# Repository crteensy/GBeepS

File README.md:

# GBeepS
GPS / Buzzer combo with backup supply

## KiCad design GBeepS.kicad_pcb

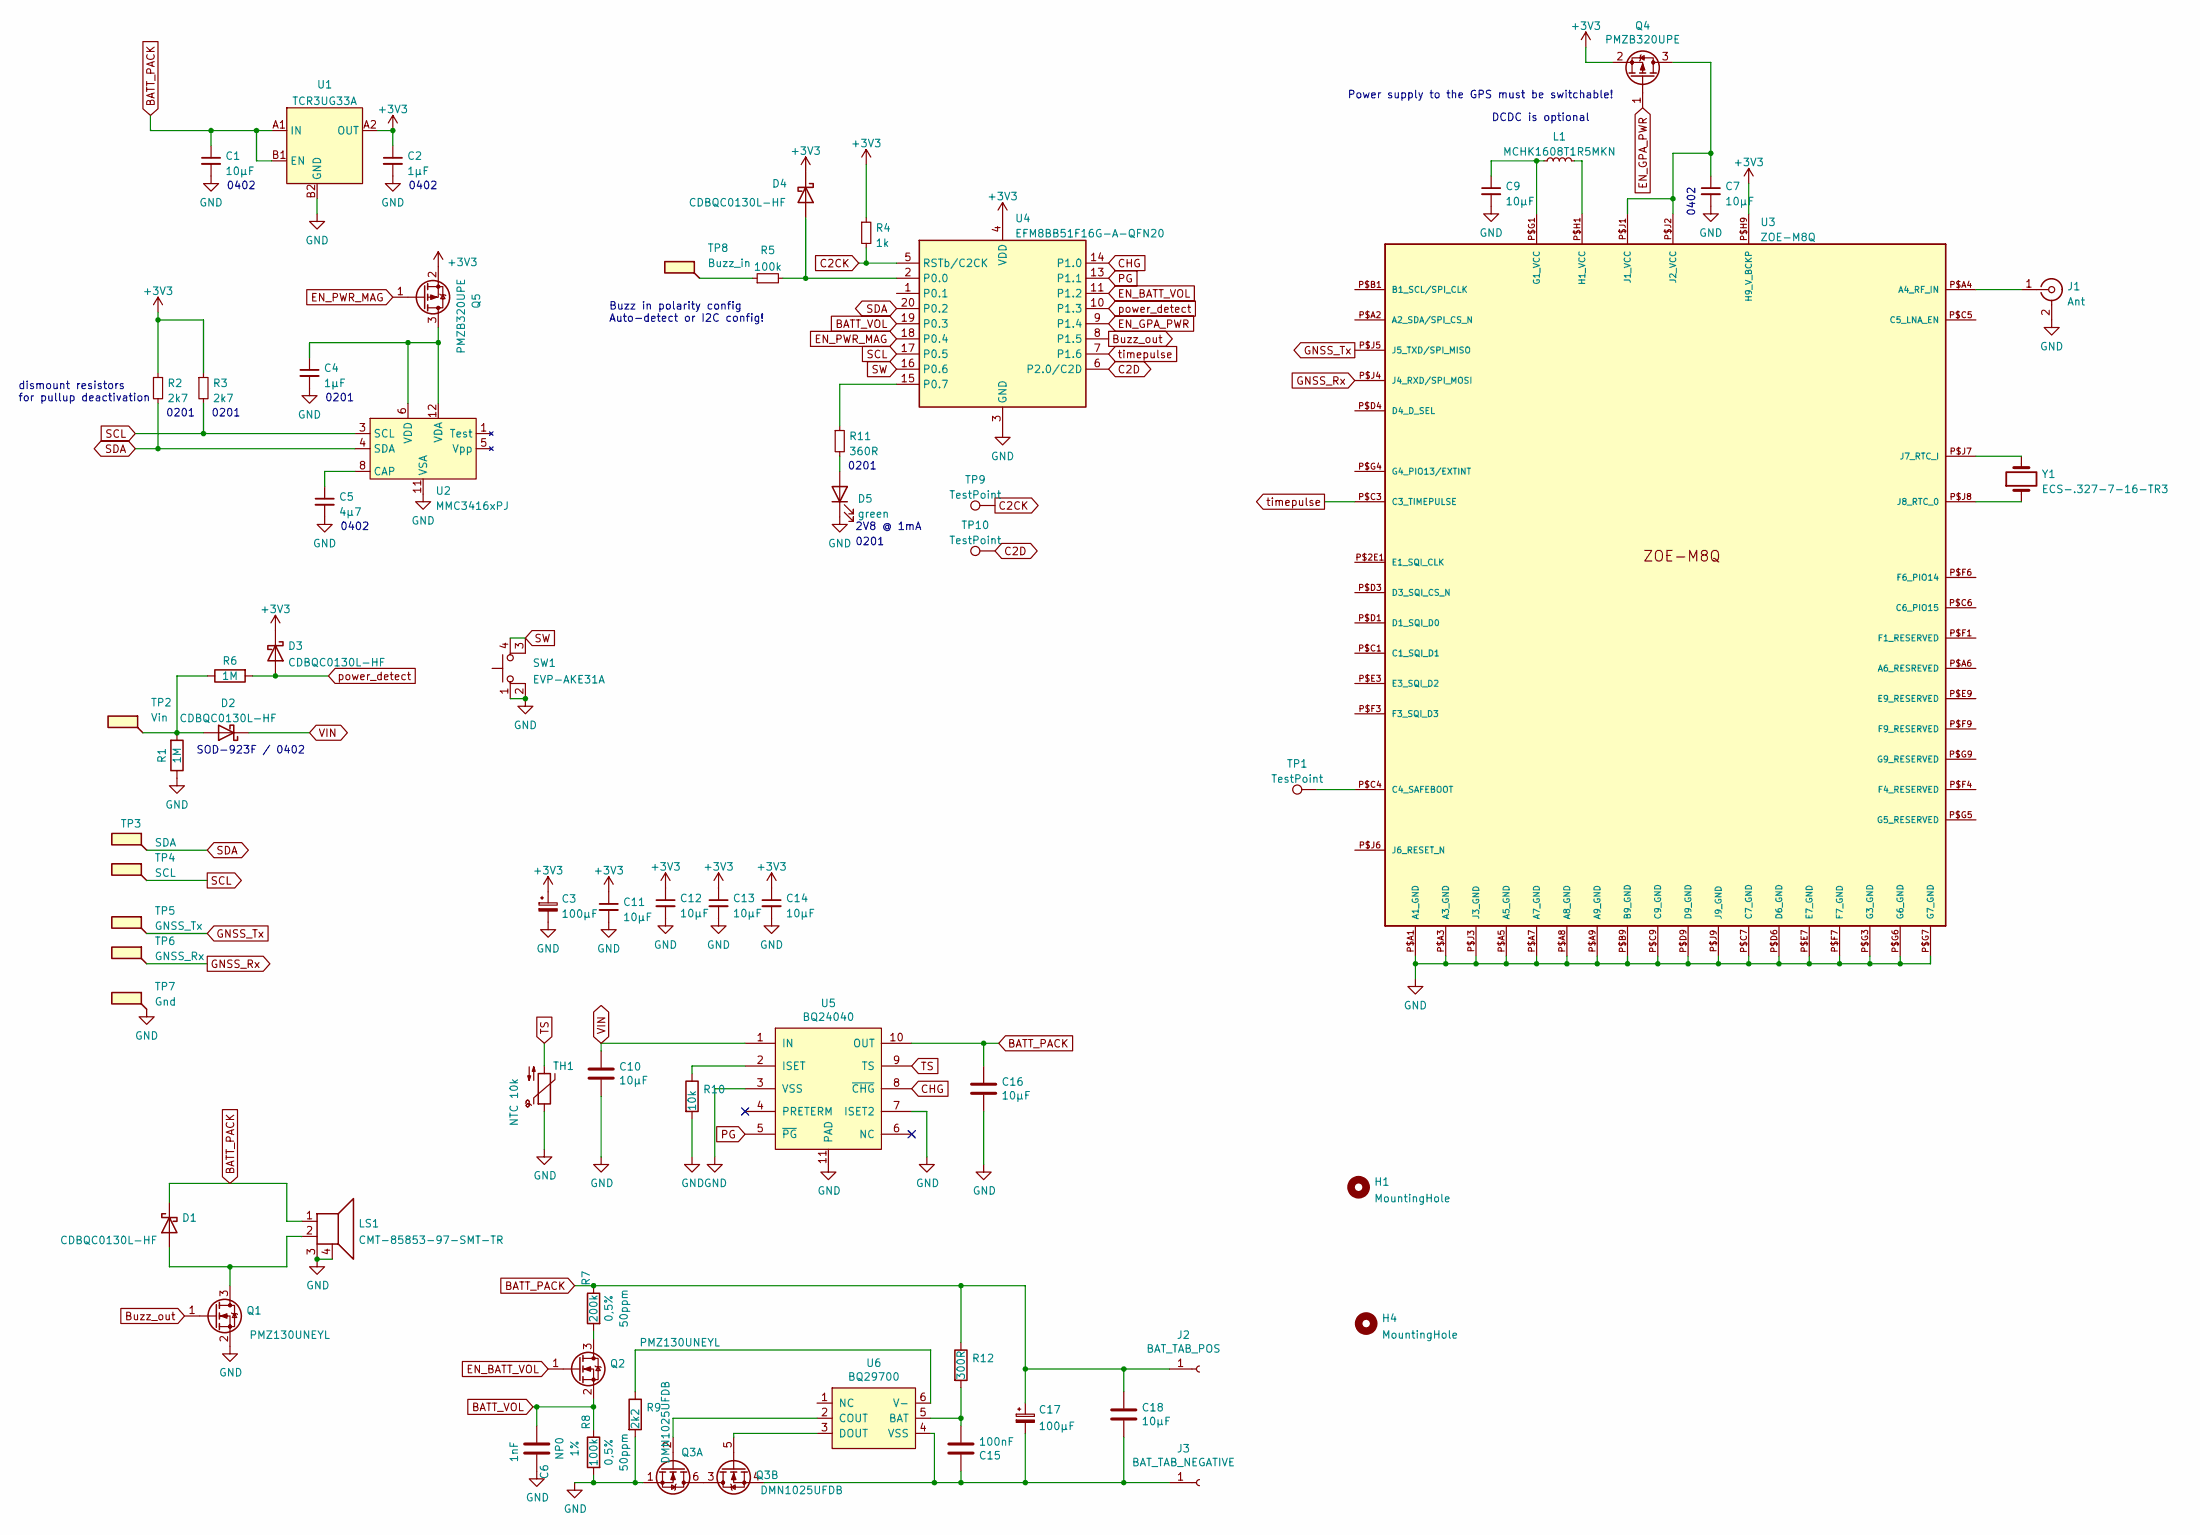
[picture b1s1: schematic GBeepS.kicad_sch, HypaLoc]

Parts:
C1, C7, C9, C11, C12, C13, C14: 10µF; C_0402_1005Metric
C2, C4: 1µF; C_0201_0603Metric_mod
C3, C17: 100µF; CP_EIA-3216-18_Kemet-A
C5: 4µ7; C_0402_1005Metric
C6: 1nF; C_0201_0603Metric_mod; MouserNr 81-GRM1555C1H102FA1D
C10, C16, C18: 10µF; C_0402_1005Metric; MouserNr 810-C1608X5R0J106KE
C15: 100nF; C_0201_0603Metric_mod; MouserNr 963-GMK105BJ104MV-F
D1, D2, D3, D4: CDBQC0130L-HF; D_SOD-932F_0402_1005Metric
D5: green; LED_0201_0603Metric
H1, H4: MountingHole; MountingHole_2.2mm_M2_DIN965_Pad
J1: Ant; U.FL_Molex_MCRF_73412-0110_Vertical
J2: BAT_TAB_POS; MountingHole_2.2mm_M2_DIN965_Pad
J3: BAT_TAB_NEGATIVE; MountingHole_2.2mm_M2_DIN965_Pad
L1: MCHK1608T1R5MKN; L_0603_1608Metric
LS1: CMT-85853-97-SMT-TR; MagneticBuzzer_CUI_CMT-8504-100-SMT
Q1, Q2: PMZ130UNEYL; Diodes_DFN1006-3
Q3: DMN1025UFDB; U-DFN2020-6-2EP; MouserNr 621-DMN1025UFDB-7
Q4, Q5: PMZB320UPE; Diodes_DFN1006-3
R1, R6: 1M; R_0201_0603Metric_mod; MouserNr 667-ERA-2ARB333X
R2, R3: 2k7; R_0201_0603Metric_mod
R4: 1k; R_0201_0603Metric_mod
R5: 100k; R_0201_0603Metric_mod
R7: 200k; R_0201_0603Metric_mod; MouserNr 667-ERA-2ARB333X
R8: 100k; R_0201_0603Metric_mod; MouserNr 667-ERA-2ARB333X
R9: 2k2; R_0201_0603Metric_mod; MouserNr 603-AC0402FR-072K26L
R10: 10k; R_0201_0603Metric_mod; MouserNr 603-AC0402FR-071K82L
R11: 360R; R_0201_0603Metric_mod
R12: 300R; R_0201_0603Metric_mod; MouserNr 603-AC0402FR-07300RL
SW1: EVP-AKE31A; EVPAV
TH1: NTC 10k; R_0402_1005Metric; MouserNr 81-NCP15XH103F03RC
TP1, TP9, TP10: TestPoint; TestPoint_Pad_D1.0mm
TP2: Vin; pad_1x1.5
TP3: SDA; pad_1x1.5
TP4: SCL; pad_1x1.5
TP5: GNSS_Tx; pad_1x1.5
TP6: GNSS_Rx; pad_1x1.5
TP7: Gnd; pad_1x1.5
TP8: Buzz_in; pad_1x1.5
U1: TCR3UG33A; WLP-4_0.73x0.73mm_Layout2x2_P0.35mm_Ball0.22mm_Pad0.2mm_NSM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
U2: MMC3416xPJ; BGA-12_4x4_1.6x1.6mm
U3: ZOE-M8Q; ZOE-M8
U4: EFM8BB51F16G-A-QFN20; SiliconLabs_QFN-20-1EP_3x3mm_P0.5mm_EP1.8x1.8mm
U5: BQ24040; WSON_10_P0.4_2x2; MouserNr BQ24040 (Texas Instruments)
U6: BQ29700; WSON-6_1.5x1.5mm_P0.5mm; MouserNr 595-BQ29700DSER
Y1: ECS-.327-7-16-TR3; Crystal_SMD_MicroCrystal_CM9V-T1A-2Pin_1.6x1.0mm

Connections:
+3V3: C2.1, C3.1, C11.1, C12.1, C13.1, C14.1, D3.1 (K), D4.1 (K), Q4.2 (S), Q5.2 (S), R2.1, R3.1, R4.1, U1.A2 (OUT), U3.P$H9 (H9_V_BCKP), U4.4 (VDD)
BATT_PACK: C1.1, C16.1, C17.1, C18.1, D1.1 (K), J2.1, LS1.1, R7.1, R12.1, U1.A1 (IN), U1.B1 (EN), U5.10 (OUT)
BATT_VOL: C6.1, Q2.2 (S), R8.1, U4.19 (P0.3)
Buzz_out: Q1.1 (G), U4.8 (P1.5)
C2CK: R4.2, TP9.1, U4.5 (RSTb/C2CK)
C2D: TP10.1, U4.6 (P2.0/C2D)
CHG: U4.14 (P1.0), U5.8 (~CHG)
EN_BATT_VOL: Q2.1 (G), U4.11 (P1.2)
EN_GPA_PWR: Q4.1 (G), U4.9 (P1.4)
EN_PWR_MAG: Q5.1 (G), U4.18 (P0.4)
GND: C1.2, C2.2, C3.2, C4.2, C5.2, C6.2, C7.2, C9.2, C10.2, C11.2, C12.2, C13.2, C14.2, C16.2, D5.1 (K), J1.2 (Ext), LS1.3 (2), LS1.4 (2), Q1.2 (S), Q3.1 (S), R1.1, R8.2, R9.2, R10.2, SW1.1, SW1.2, TH1.1, TP7.1, U1.B2 (GND), U2.11 (VSA), U3.P$A1 (A1_GND), U3.P$A3 (A3_GND), U3.P$A5 (A5_GND), U3.P$A7 (A7_GND), U3.P$A8 (A8_GND), U3.P$A9 (A9_GND), U3.P$B9 (B9_GND), U3.P$C7 (C7_GND), U3.P$C9 (C9_GND), U3.P$D6 (D6_GND), U3.P$D9 (D9_GND), U3.P$E7 (E7_GND), U3.P$F7 (F7_GND), U3.P$G3 (G3_GND), U3.P$G6 (G6_GND), U3.P$G7 (G7_GND), U3.P$J3 (J3_GND), U3.P$J9 (J9_GND), U4.3 (GND), U4.12 (GND), U4.21 (GND), U5.3 (VSS), U5.7 (ISET2), U5.11 (PAD)
GNSS_Rx: TP6.1, U3.P$J4 (J4_RXD/SPI_MOSI)
GNSS_Tx: TP5.1, U3.P$J5 (J5_TXD/SPI_MISO)
unnamed: C4.1, Q5.3 (D), U2.6 (VDD), U2.12 (VDA)
unnamed: C5.1, U2.8 (CAP)
unnamed: C7.1, Q4.3 (D), U3.P$J1 (J1_VCC), U3.P$J2 (J2_VCC)
unnamed: C9.1, L1.1, U3.P$G1 (G1_VCC)
unnamed: C15.1, C17.2, C18.2, J3.1, Q3.4 (S), U6.4 (VSS)
unnamed: C15.2, R12.2, U6.5 (BAT)
unnamed: D1.2 (A), LS1.2, Q1.3 (D)
unnamed: D2.2 (A), R1.2, R6.1, TP2.1
unnamed: D4.2 (A), R5.2, U4.2 (P0.0)
unnamed: D5.2 (A), R11.2
unnamed: J1.1 (In), U3.P$A4 (A4_RF_IN)
unnamed: L1.2, U3.P$H1 (H1_VCC)
unnamed: Q2.3 (D), R7.2
unnamed: Q3.2 (G), U6.2 (COUT)
unnamed: Q3.3 (D), Q3.6 (D)
unnamed: Q3.5 (G), U6.3 (DOUT)
unnamed: R5.1, TP8.1
unnamed: R9.1, U6.6 (V-)
unnamed: R10.1, U5.2 (ISET)
unnamed: R11.1, U4.15 (P0.7)
unnamed: TP1.1, U3.P$C4 (C4_SAFEBOOT)
unnamed: U3.P$J7 (J7_RTC_I), Y1.2
unnamed: U3.P$J8 (J8_RTC_0), Y1.1
PG: U4.13 (P1.1), U5.5 (~PG)
SCL: R3.2, TP4.1, U2.3 (SCL), U4.17 (P0.5)
SDA: R2.2, TP3.1, U2.4 (SDA), U4.20 (P0.2)
SW: SW1.3 (K), SW1.4 (A), U4.16 (P0.6)
TS: TH1.2, U5.9 (TS)
VIN: C10.1, D2.1 (K), U5.1 (IN)
power_detect: D3.2 (A), R6.2, U4.10 (P1.3)
timepulse: U3.P$C3 (C3_TIMEPULSE), U4.7 (P1.6)

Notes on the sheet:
Power supply to the GPS must be switchable!
Buzz in polarity config Auto-detect or I2C config!
0201
0402
2V8 @ 1mA
DCDC is optional
SOD-923F / 0402
dismount resistors for pullup deactivation

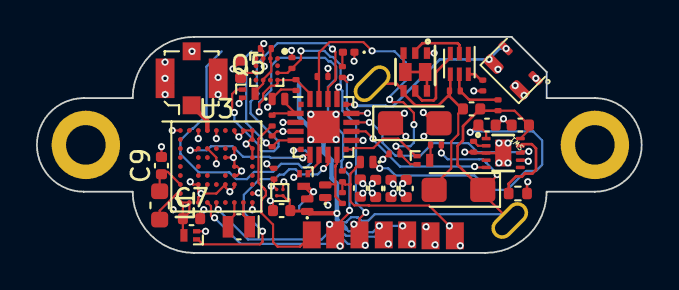
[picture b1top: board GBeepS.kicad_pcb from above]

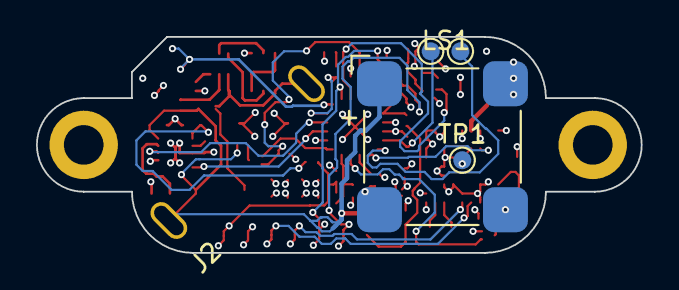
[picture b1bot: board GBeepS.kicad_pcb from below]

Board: 4 copper layers, 33.6 x 12.0 mm, 65 parts (5 on the bottom side), 44 nets.

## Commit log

2022-06-04 update schematic
2022-06-05 added battery stuff
2022-06-06 rudimentary layout and 3D models
2022-06-06 update layout
2022-06-12 started routing
2022-06-12 saved schematic
2022-06-22 added pushbutton and routed everything
